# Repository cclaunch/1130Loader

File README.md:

# 1130Loader

This is a minor enhancement to an IBM 1130 that allows users to enter commands from a PC either directly or through a file, entering data words into core. This will be version 5 of the design, a significant change. 

Manually toggling in programs is a time consuming affair, flipping the 16 Console Entry Switches and pushing the Program Start button to enter each word sequentially. Every change in the area of core to be loaded requires that the address be set in those entry switches and the Load IAR button be pressed.

This device utilizes the cycle steal capability of the 1130, where peripheral controllers can read or write locations in memory by causing the CPU to pause while a memory cycle is used for the peripheral, then the CPU instruction processing continues. This is very similar to DMA on a microprocessor. 

When used with a terminal program that will send lines of a text file when it receives the prompt character from the loader, this allows files to be prepared to load into core of the 1130 in a rapid and reliable way. The format of the text file was chosen to match the simh based IBM 1130 Simulator memory dump format, thus programs can be tested on the simulator, dumped to files and loaded onto the physical 1130 system for execution. The format is to place each word as four ASCII characters represening the four hex digits. If the four digit line is prefixed by the command character @, the value is loaded into the 1130 IAR to set the location for subsequent memory words. If the line is prefixed by the command character Z it loads words of 0000 into as many locations as the four hex digits specify. If the command character prefix is =, the four digit value is saved and at the end of the loading, the IAR will be set to this value as the starting point for execution. Finally the command character # entered on a line by itself will toggle the loader to activation or deactivate it. Thus each simulator memory dump file needs to have a # line added at the front and at the end. 

To use the loader, connect a serial connection to the USB connector on the 1130 and open the terminal program. The 1130 must be stopped for this to runction, otherwise nothing special is needed. 

Physically the loader consists of an Arduino Mega 2560 and a custom shield that interfaces it to the IBM 1130. This is mounted on the logic gate B, connected to header boards on the gate which are then connected to individual backplane (board) pins using wirewrap. 

The code allows you to substitute different command characters and change the prompt character.

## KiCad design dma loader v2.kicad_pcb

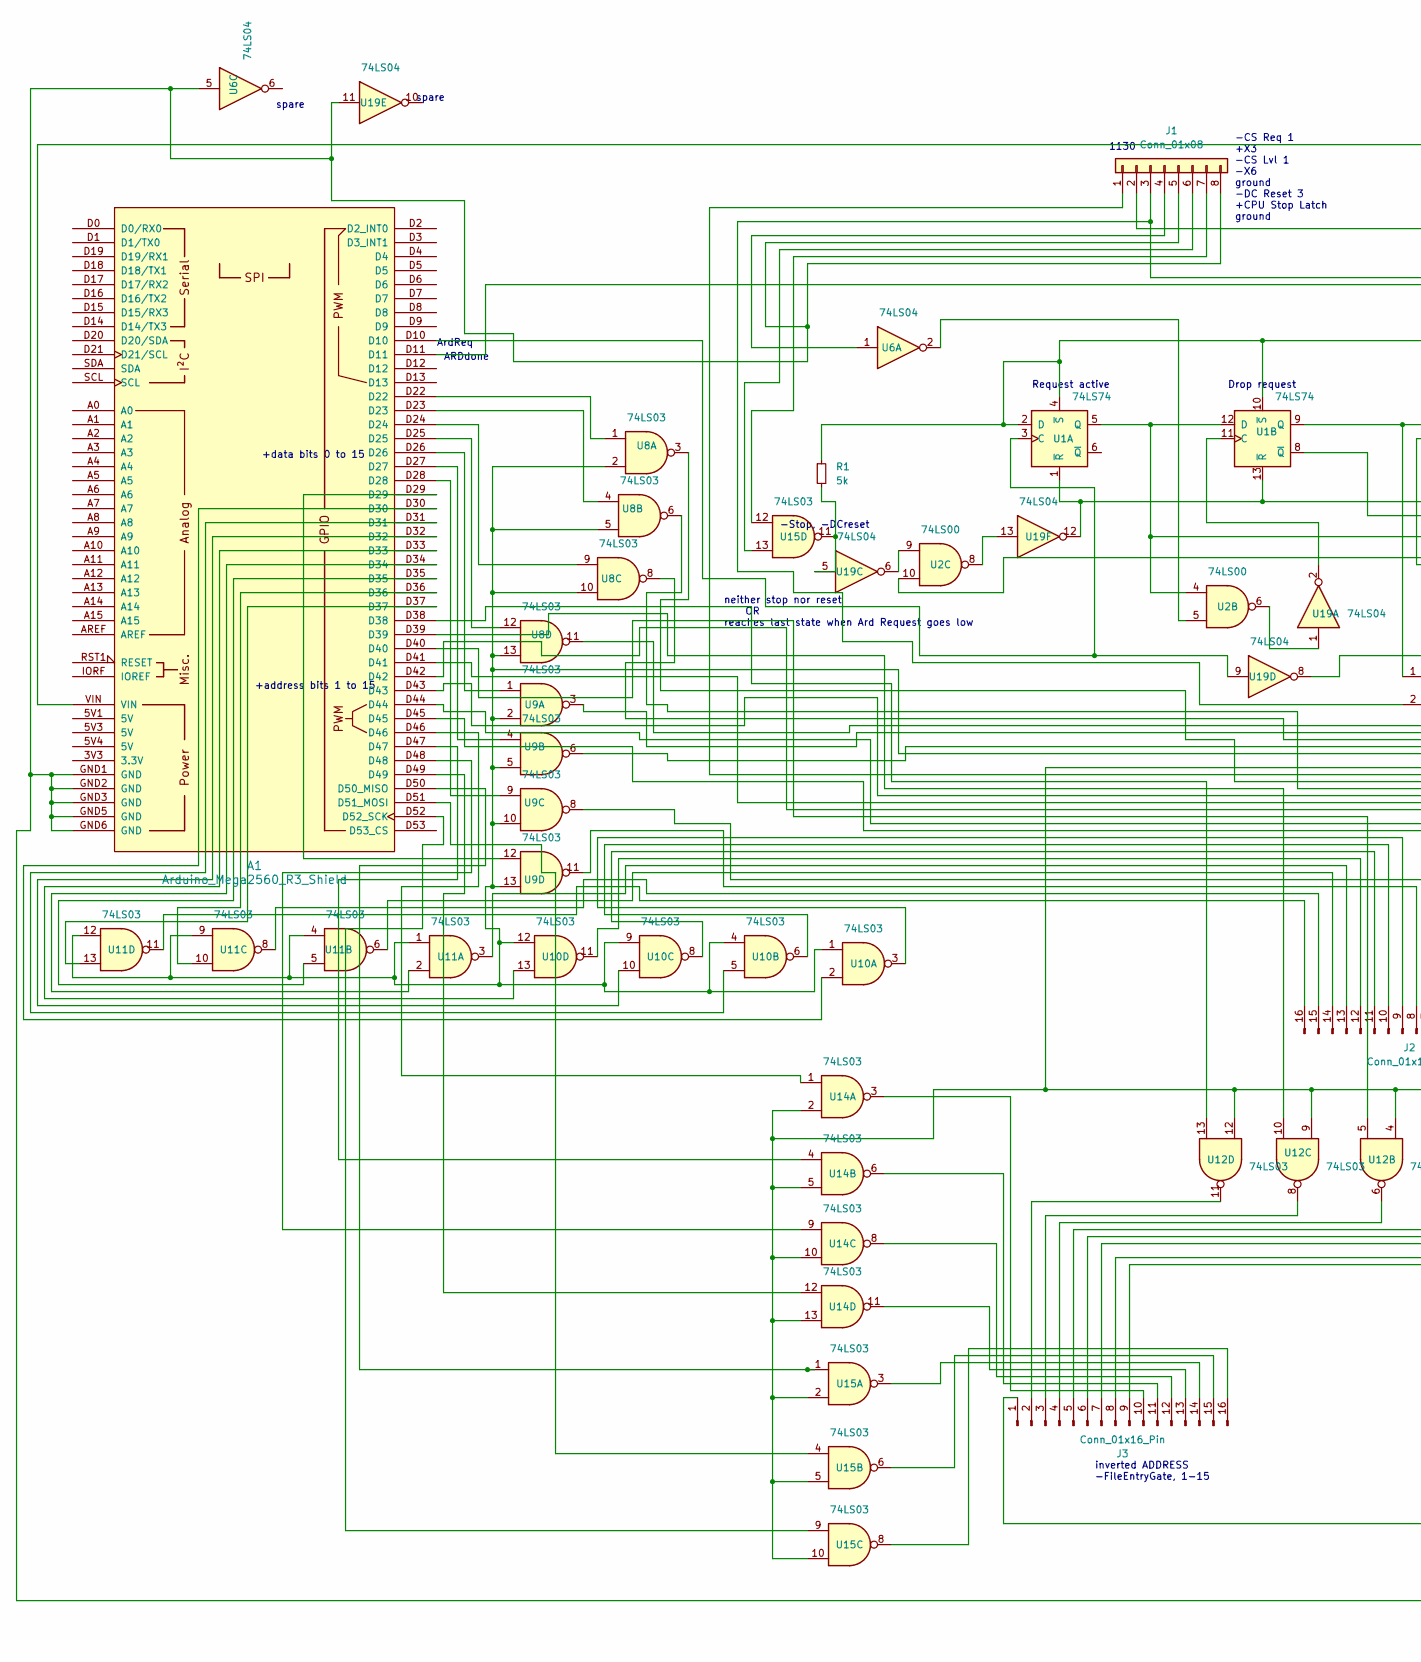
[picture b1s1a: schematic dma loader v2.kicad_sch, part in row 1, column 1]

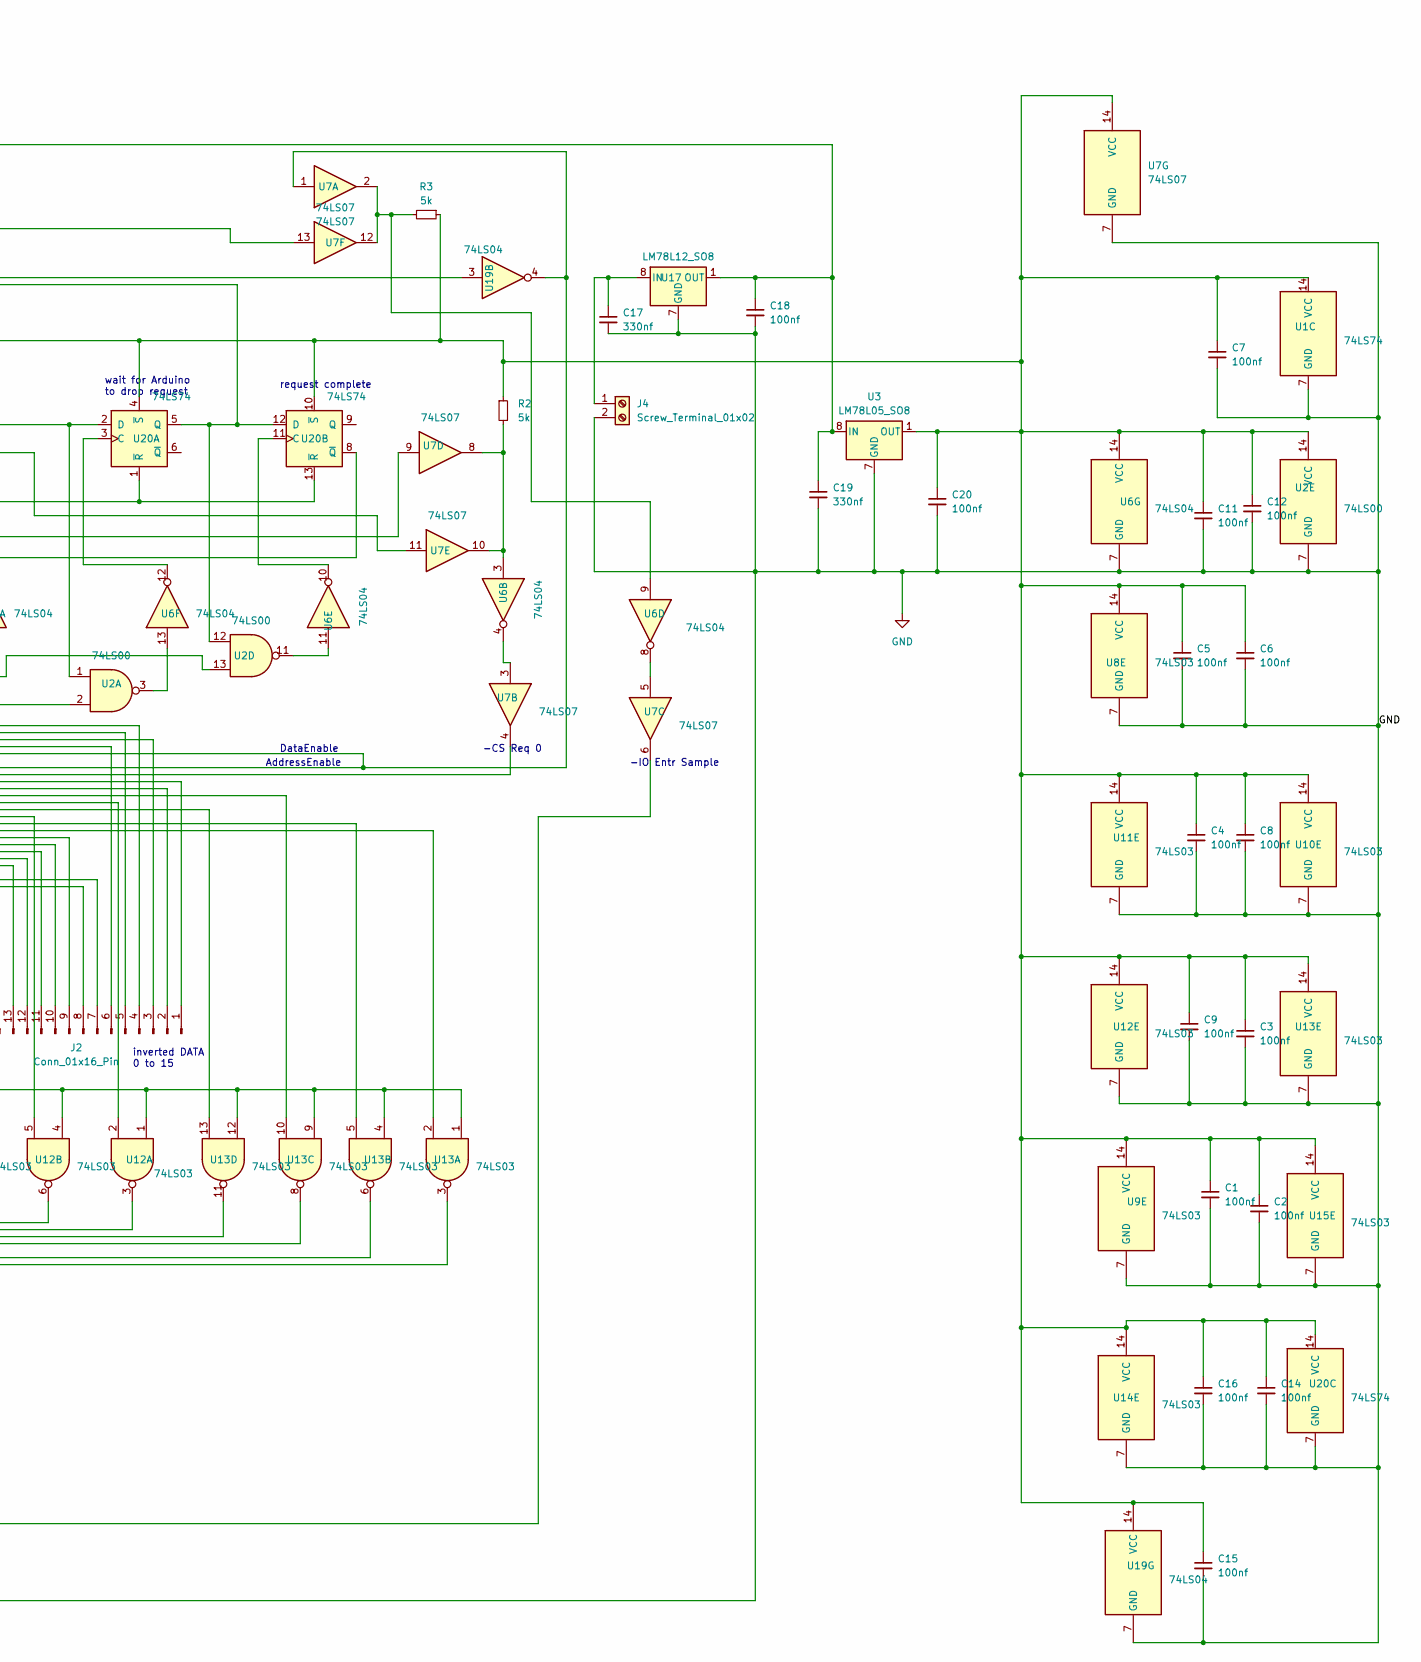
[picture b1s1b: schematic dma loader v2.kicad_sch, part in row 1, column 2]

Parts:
A1: Arduino_Mega2560_R3_Shield
C1, C2, C3, C4, C5, C6, C7, C8, C9, C11, C12, C14, C15, C16, C18, C20: 100nf; C_0805_2012Metric_Pad1.18x1.45mm_HandSolder
C17, C19: 330nf; C_0805_2012Metric_Pad1.18x1.45mm_HandSolder
J1: Conn_01x08; PinHeader_1x08_P2.54mm_Vertical
J2, J3: Conn_01x16_Pin; PinHeader_1x16_P2.54mm_Vertical
J4: Screw_Terminal_01x02; PhoenixContact_MSTBA_2,5_2-G_1x02_P5.00mm_Horizontal
R1, R2, R3: 5k; R_0805_2012Metric_Pad1.20x1.40mm_HandSolder
U1, U20: 74LS74; SOIC-14_3.9x8.7mm_P1.27mm
U2: 74LS00; SOIC-14_3.9x8.7mm_P1.27mm
U3: LM78L05_SO8; SOIC-8_3.9x4.9mm_P1.27mm
U6, U19: 74LS04; SOIC-14_3.9x8.7mm_P1.27mm
U7: 74LS07; SOIC-14_3.9x8.7mm_P1.27mm
U8, U9, U10, U11, U12, U13, U14, U15: 74LS03; SOIC-14_3.9x8.7mm_P1.27mm
U17: LM78L12_SO8; SOIC-8_3.9x4.9mm_P1.27mm

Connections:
GND: A1.GND1 (GND), A1.GND2 (GND), A1.GND3 (GND), A1.GND5 (GND), A1.GND6 (GND), C1.2, C2.2, C3.2, C4.2, C5.2, C6.2, C7.2, C8.2, C9.2, C11.2, C12.2, C14.2, C15.2, C16.2, C17.2, C18.2, C19.2, C20.2, J1.5, J1.8, J4.2, U1.7 (GND), U2.7 (GND), U3.2 (GND), U3.3 (GND), U3.6 (GND), U3.7 (GND), U6.5, U6.7 (GND), U7.7 (GND), U8.7 (GND), U9.7 (GND), U10.7 (GND), U11.7 (GND), U12.7 (GND), U13.7 (GND), U14.7 (GND), U15.7 (GND), U17.2 (GND), U17.3 (GND), U17.6 (GND), U17.7 (GND), U19.7 (GND), U19.11, U20.7 (GND)
unnamed: A1.D50 (D50_MISO), U15.1
unnamed: A1.D51 (D51_MOSI), U15.4
unnamed: A1.D52 (D52_SCK), U15.9
unnamed: A1.D22, U8.1
unnamed: A1.D23, U8.4
unnamed: A1.D24, U8.9
unnamed: A1.D25, U8.12
unnamed: A1.D26, U9.1
unnamed: A1.D27, U9.4
unnamed: A1.D28, U9.9
unnamed: A1.D29, U9.12
unnamed: A1.D30, U10.2
unnamed: A1.D31, U10.5
unnamed: A1.D32, U10.10
unnamed: A1.D33, U10.13
unnamed: A1.D34, U11.2
unnamed: A1.D35, U11.5
unnamed: A1.D36, U11.10
unnamed: A1.D37, U11.13
unnamed: A1.D38, U12.13
unnamed: A1.D39, U12.10
unnamed: A1.D40, U12.5
unnamed: A1.D41, U12.2
unnamed: A1.D42, U13.13
unnamed: A1.D43, U13.10
unnamed: A1.D44, U13.5
unnamed: A1.D45, U13.2
unnamed: A1.D46, U14.1
unnamed: A1.D47, U14.4
unnamed: A1.D48, U14.9
unnamed: A1.D49, U14.12
unnamed: J1.1, U7.4
unnamed: J1.2, U7.13
unnamed: J1.3, U2.2, U19.3
unnamed: J1.4, U6.1
unnamed: J1.6, U15.13
unnamed: J1.7, U15.12
unnamed: J2.1, U8.3
unnamed: J2.2, U8.6
unnamed: J2.3, U8.8
unnamed: J2.4, U8.11
unnamed: J2.5, U9.3
unnamed: J2.6, U9.6
unnamed: J2.7, U9.8
unnamed: J2.8, U9.11
unnamed: J2.9, U10.3
unnamed: J2.10, U10.6
unnamed: J2.11, U10.8
unnamed: J2.12, U10.11
unnamed: J2.13, U11.3
unnamed: J2.14, U11.6
unnamed: J2.15, U11.8
unnamed: J2.16, U11.11
unnamed: J3.1, U7.6
unnamed: J3.2, U12.11
unnamed: J3.3, U12.8
unnamed: J3.4, U12.6
unnamed: J3.5, U12.3
unnamed: J3.6, U13.11
unnamed: J3.7, U13.8
unnamed: J3.8, U13.6
unnamed: J3.9, U13.3
unnamed: J3.10, U14.3
unnamed: J3.11, U14.6
unnamed: J3.12, U14.8
unnamed: J3.13, U14.11
unnamed: J3.14, U15.3
unnamed: J3.15, U15.6
unnamed: J3.16, U15.8
unnamed: C17.1, J4.1, U17.8 (IN)
unnamed: R1.2, U15.11, U19.5
unnamed: R2.2, U6.3, U7.8, U7.10
unnamed: R3.2, U6.9, U7.2, U7.12
unnamed: A1.D10, U1.3 (C), U19.9
unnamed: U1.5 (Q), U1.12 (D), U2.4, U7.9
unnamed: U1.1 (~R), U1.13 (~R), U19.12, U20.1 (~R), U20.13 (~R)
unnamed: U1.11 (C), U19.2
unnamed: U1.9 (Q), U2.1, U20.2 (D)
unnamed: U1.8 (~Q), U7.11
unnamed: U2.3, U6.13
unnamed: U2.5, U6.2
unnamed: U2.11, U6.11
unnamed: U6.4, U7.3
unnamed: U6.8, U7.5
unnamed: U7.1, U8.2, U8.5, U8.10, U8.13, U9.2, U9.5, U9.10, U9.13, U10.1, U10.4, U10.9, U10.12, U11.1, U11.4, U11.9, U11.12, U12.1, U12.4, U12.9, U12.12, U13.1, U13.4, U13.9, U13.12, U14.2, U14.5, U14.10, U14.13, U15.2, U15.5, U15.10, U19.4
unnamed: C1.1, C2.1, C3.1, C4.1, C5.1, C6.1, C7.1, C8.1, C9.1, C11.1, C12.1, C14.1, C15.1, C16.1, C20.1, R1.1, R2.1, R3.1, U1.2 (D), U1.4 (~S), U1.10 (~S), U1.14 (VCC), U2.14 (VCC), U3.1 (OUT), U6.14 (VCC), U7.14 (VCC), U8.14 (VCC), U9.14 (VCC), U10.14 (VCC), U11.14 (VCC), U12.14 (VCC), U13.14 (VCC), U14.14 (VCC), U15.14 (VCC), U19.14 (VCC), U20.4 (~S), U20.10 (~S), U20.14 (VCC)
unnamed: A1.VIN, C18.1, C19.1, U3.8 (IN), U17.1 (OUT)
unnamed: U2.6, U19.1
unnamed: U2.9, U19.6
unnamed: U2.13, U19.8
unnamed: U2.8, U19.13
unnamed: U6.12, U20.3 (C)
unnamed: A1.D11, U2.12, U20.5 (Q), U20.12 (D)
unnamed: U6.10, U20.11 (C)
unnamed: U2.10, U20.8 (~Q)

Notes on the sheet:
+data bits 0 to 15
-CS Req 0
-IO Entr Sample
-Stop, -DCreset
spare
neither stop nor reset OR reaches last state when Ard Request goes low
ARDdone
Request active
1130
AddressEnable
-CS Req 1 +X3 -CS Lvl 1 -X6 ground -DC Reset 3 +CPU Stop Latch ground
+address bits 1 to 15
inverted DATA 0 to 15
request complete
ArdReq
wait for Arduino to drop request
DataEnable
inverted ADDRESS -FileEntryGate, 1-15
Drop request

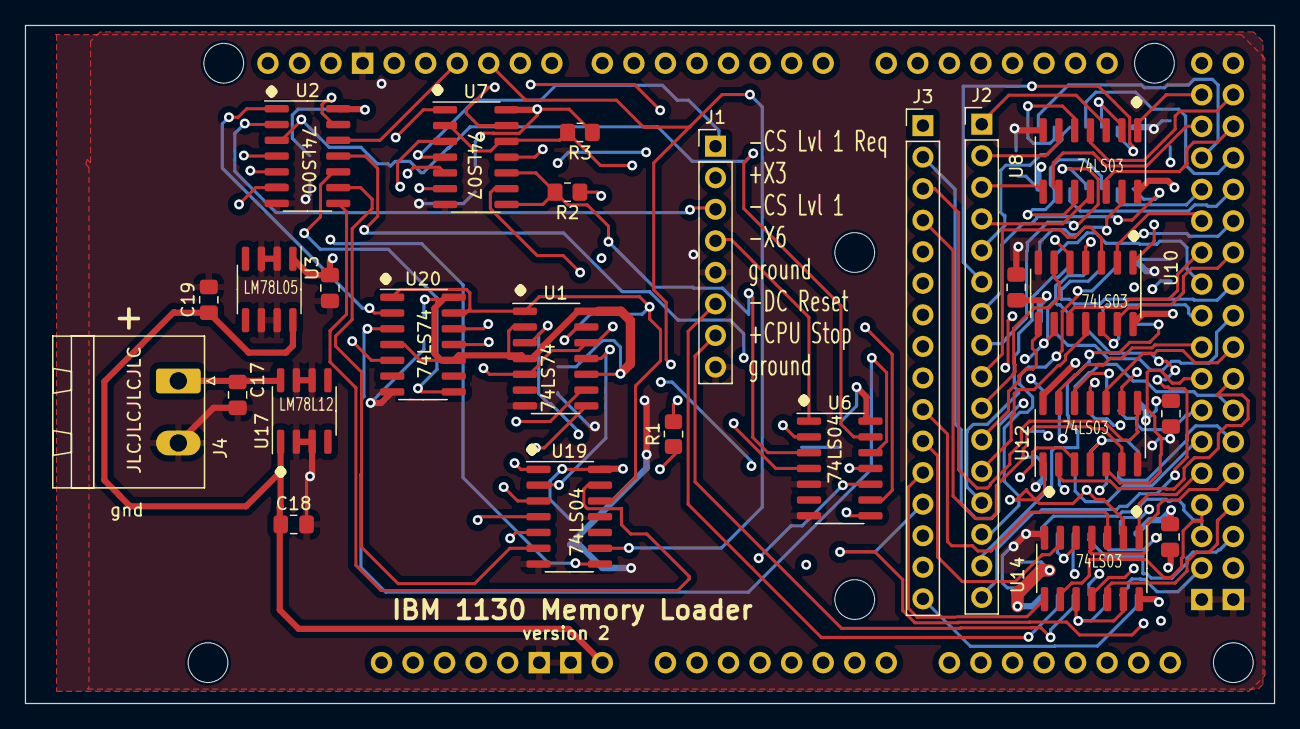
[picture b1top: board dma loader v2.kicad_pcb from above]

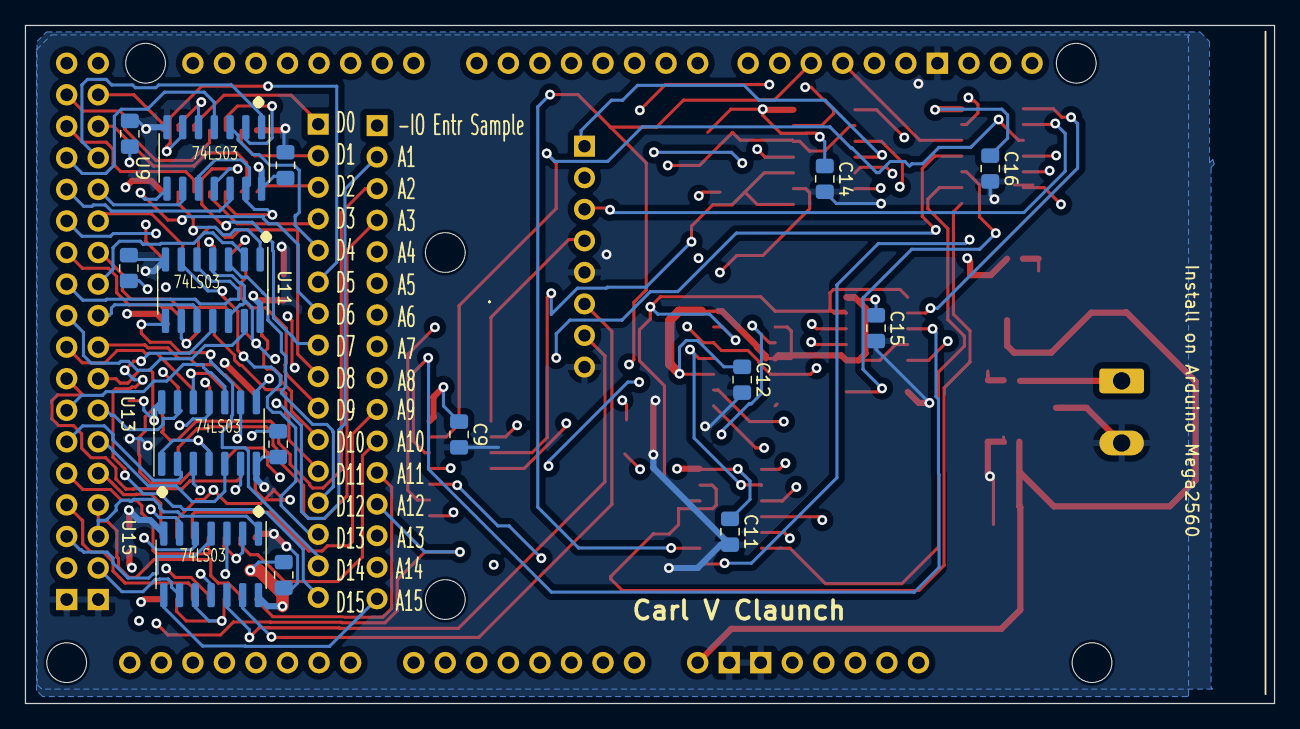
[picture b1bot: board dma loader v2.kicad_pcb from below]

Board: 4 copper layers, 100.6 x 54.6 mm, 42 parts (15 on the bottom side), 96 nets.

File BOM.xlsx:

Part number | Value | Size | Vendor | vendor number
U1 | 74LS74 | 14SOIC | Digikey | 296-14899-1-ND
U2 | 74LS00 | 14SOIC | Digikey | 296-14873-1-ND
U3 | LM78L05 | S08 | Mouser | 926-LM78L05ACMX/NOPB
U6 | 74LS04 | 14SOIC | Digikey | 296-14875-1-ND
U7 | 74LS07 | 14SOIC | Digikey | 296-14877-1-ND
U8 | 74LS03 | 14SOIC | Digikey | 296-33951-5-ND
U9 | 74LS03 | 14SOIC | Digikey | 296-33951-5-ND
U10 | 74LS03 | 14SOIC | Digikey | 296-33951-5-ND
U11 | 74LS03 | 14SOIC | Digikey | 296-33951-5-ND
U12 | 74LS03 | 14SOIC | Digikey | 296-33951-5-ND
U13 | 74LS03 | 14SOIC | Digikey | 296-33951-5-ND
U14 | 74LS03 | 14SOIC | Digikey | 296-33951-5-ND
U15 | 74LS03 | 14SOIC | Digikey | 296-33951-5-ND
U17 | LM78L12 | S08 | Digikey | 296-LM78L12ACMX/NOPBCT-ND
U19 | 74LS04 | 14SOIC | Digikey | 296-14875-1-ND
U20 | 74LS74 | 14SOIC | Digikey | 296-14899-1-ND
R1 | 5K | 0805 | Digikey | 541-CRCW08055K00JNTACT-ND
R2 | 5K | 0805 | Digikey | 541-CRCW08055K00JNTACT-ND
R3 | 5K | 0805 | Digikey | 541-CRCW08055K00JNTACT-ND
J1 | 1x8 | 2.54mm | Digikey | 2057-PH1-08-UA-ND
J2 | 1x16 | 2.54mm | Digikey | 2057-PH1-16-UA-ND
J3 | 1x16 | 2.54mm | Digikey | 2057-PH1-16-UA-ND
J4 | 1x2 |  | Digikey | 277-1236-ND
C1 | 100nf | 0805 | Digikey | 478-KGM21NR71H104KTCT-ND
C2 | 100nf | 0805 | Digikey | 478-KGM21NR71H104KTCT-ND
C3 | 100nf | 0805 | Digikey | 478-KGM21NR71H104KTCT-ND
C4 | 100nf | 0805 | Digikey | 478-KGM21NR71H104KTCT-ND
C5 | 100nf | 0805 | Digikey | 478-KGM21NR71H104KTCT-ND
C6 | 100nf | 0805 | Digikey | 478-KGM21NR71H104KTCT-ND
C7 | 100nf | 0805 | Digikey | 478-KGM21NR71H104KTCT-ND
C8 | 100nf | 0805 | Digikey | 478-KGM21NR71H104KTCT-ND
C9 | 100nf | 0805 | Digikey | 478-KGM21NR71H104KTCT-ND
C11 | 100nf | 0805 | Digikey | 478-KGM21NR71H104KTCT-ND
C12 | 100nf | 0805 | Digikey | 478-KGM21NR71H104KTCT-ND
C13 | 100nf | 0805 | Digikey | 478-KGM21NR71H104KTCT-ND
C14 | 100nf | 0805 | Digikey | 478-KGM21NR71H104KTCT-ND
C15 | 100nf | 0805 | Digikey | 478-KGM21NR71H104KTCT-ND
C16 | 100nf | 0805 | Digikey | 478-KGM21NR71H104KTCT-ND
C17 | 330nf | 0805 | Digikey | 490-14413-1-ND
C18 | 100nf | 0805 | Digikey | 478-KGM21NR71H104KTCT-ND
C19 | 330nf | 0805 | Digikey | 490-14413-1-ND
C20 | 100nf | 0805 | Digikey | 478-KGM21NR71H104KTCT-ND
A1 | 1x10 | 2.54mm | Digikey | 2057-PH1-10-UA-ND
A2 | 1x8 | 2.54mm | Digikey | 2057-PH1-08-UA-ND
A3 | 1x8 | 2.54mm | Digikey | 2057-PH1-08-UA-ND
A4 | 2x20 | 2.54mm | Digikey | 2057-PH2-20-UA-ND
A5 | 1x8 | 2.54mm | Digikey | 2057-PH1-08-UA-ND
A6 | 1x8 | 2.54mm | Digikey | 2057-PH1-08-UA-ND
A7 | 1x8 | 2.54mm | Digikey | 2057-PH1-08-UA-ND
P1 | 1x8 | 2.54mm | Mouser | 200-IDSS08D2000GR
P2 | 1x16 | 2.54mm | Mouser | 200-IDSS16D2000
P3 | 1x16 | 2.54mm | Mouser | 200-IDSS16D2000

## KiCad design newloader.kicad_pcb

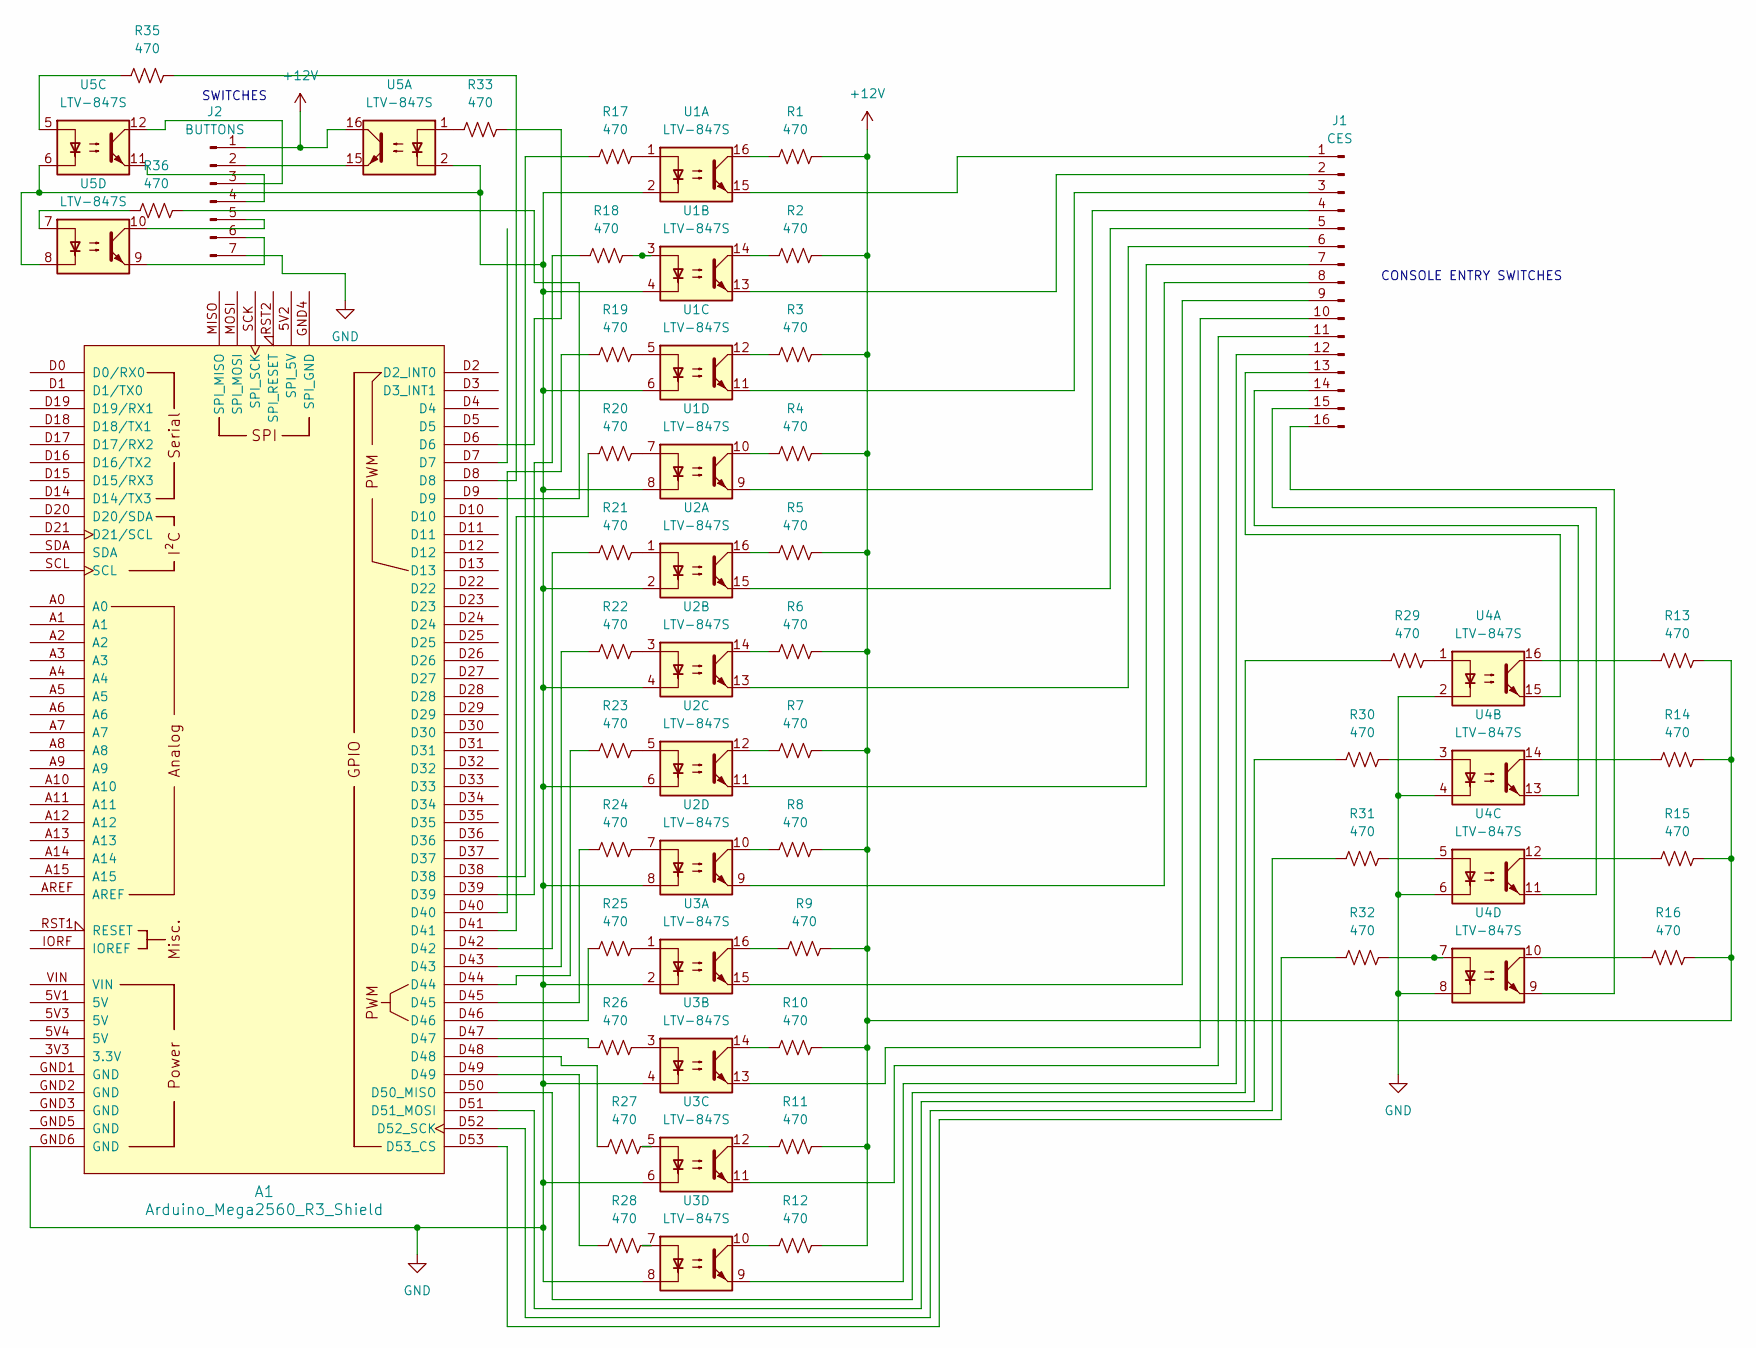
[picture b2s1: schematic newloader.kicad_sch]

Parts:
A1: Arduino_Mega2560_R3_Shield
J1: CES; PinHeader_1x16_P2.54mm_Vertical_SMD_Pin1Right
J2: BUTTONS; PinHeader_1x07_P2.54mm_Vertical_SMD_Pin1Left
R1, R2, R3, R4, R5, R6, R7, R8, R9, R10, R11, R12, R13, R14, R15, R16, R17, R18, R19, R20, R21, R22, R23, R24, R25, R26, R27, R28, R29, R30, R31, R32, R33, R35, R36: 470; R_0805_2012Metric
U1, U2, U3, U4, U5: LTV-847S; SMDIP-16_W9.53mm

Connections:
+12V: J2.1, R1.1, R2.1, R3.1, R4.1, R5.1, R6.1, R7.1, R8.1, R9.1, R10.1, R11.1, R12.1, R13.1, R14.1, R15.1, R16.1, U5.16
GND: A1.GND6 (GND), J2.7, U1.2, U1.4, U1.6, U1.8, U2.2, U2.4, U2.6, U2.8, U3.2, U3.4, U3.6, U3.8, U4.2, U4.4, U4.6, U4.8, U5.2, U5.6, U5.8
unnamed: A1.D50 (D50_MISO), R29.2
unnamed: A1.D51 (D51_MOSI), R30.2
unnamed: A1.D52 (D52_SCK), R31.2
unnamed: A1.D53 (D53_CS), R32.2
unnamed: A1.D6, R33.1
unnamed: A1.D8, R35.1
unnamed: A1.D9, R36.1
unnamed: A1.D38, R17.2
unnamed: A1.D39, R18.2
unnamed: A1.D40, R19.2
unnamed: A1.D41, R20.2
unnamed: A1.D42, R21.2
unnamed: A1.D43, R22.2
unnamed: A1.D44, R23.2
unnamed: A1.D45, R24.2
unnamed: A1.D46, R25.2
unnamed: A1.D47, R26.2
unnamed: A1.D48, R27.2
unnamed: A1.D49, R28.2
unnamed: J1.1, U1.15
unnamed: J1.2, U1.13
unnamed: J1.3, U1.11
unnamed: J1.4, U1.9
unnamed: J1.5, U2.15
unnamed: J1.6, U2.13
unnamed: J1.7, U2.11
unnamed: J1.8, U2.9
unnamed: J1.9, U3.15
unnamed: J1.10, U3.13
unnamed: J1.11, U3.11
unnamed: J1.12, U3.9
unnamed: J1.13, U4.15
unnamed: J1.14, U4.13
unnamed: J1.15, U4.11
unnamed: J1.16, U4.9
unnamed: J2.2, U5.15
unnamed: J2.3, U5.12
unnamed: J2.4, U5.11
unnamed: J2.5, U5.10
unnamed: J2.6, U5.9
unnamed: R1.2, U1.16
unnamed: R2.2, U1.14
unnamed: R3.2, U1.12
unnamed: R4.2, U1.10
unnamed: R5.2, U2.16
unnamed: R6.2, U2.14
unnamed: R7.2, U2.12
unnamed: R8.2, U2.10
unnamed: R9.2, U3.16
unnamed: R10.2, U3.14
unnamed: R11.2, U3.12
unnamed: R12.2, U3.10
unnamed: R13.2, U4.16
unnamed: R14.2, U4.14
unnamed: R15.2, U4.12
unnamed: R16.2, U4.10
unnamed: R17.1, U1.1
unnamed: R18.1, U1.3
unnamed: R19.1, U1.5
unnamed: R20.1, U1.7
unnamed: R21.1, U2.1
unnamed: R22.1, U2.3
unnamed: R23.1, U2.5
unnamed: R24.1, U2.7
unnamed: R25.1, U3.1
unnamed: R26.1, U3.3
unnamed: R27.1, U3.5
unnamed: R28.1, U3.7
unnamed: R29.1, U4.1
unnamed: R30.1, U4.3
unnamed: R31.1, U4.5
unnamed: R32.1, U4.7
unnamed: R33.2, U5.1
unnamed: R35.2, U5.5
unnamed: R36.2, U5.7

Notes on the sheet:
SWITCHES
CONSOLE ENTRY SWITCHES

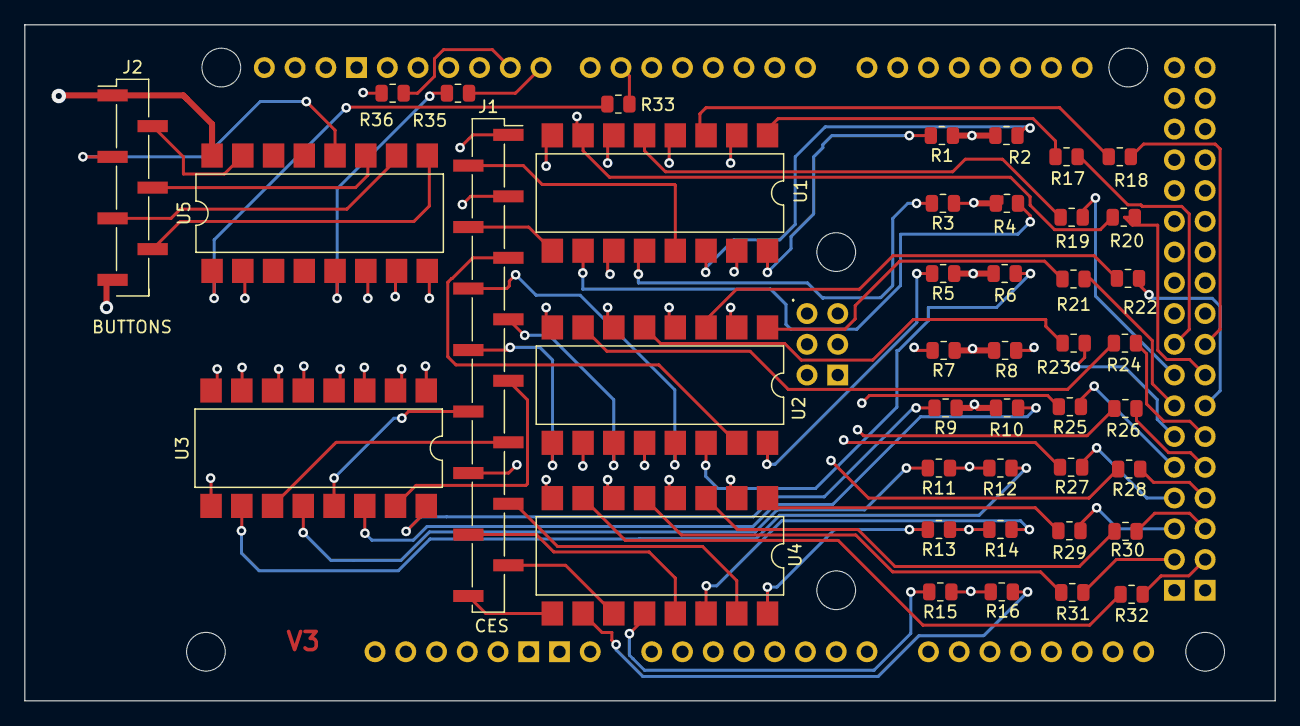
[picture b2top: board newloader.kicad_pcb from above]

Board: 4 copper layers, 103.3 x 55.8 mm, 43 parts (0 on the bottom side), 77 nets.

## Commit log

2018-05-01 Add files via upload
    Fixed defect in the order of deactivation compared to loading the IAR
2023-11-15 Document Version 2 of the project, partial update
2023-11-15 tweak to document
2023-11-15 Version 2 of Arduino code
2023-11-15 Version 2 update
2023-11-15 First upload of V2 shield PCB layout (KiCAD)
2023-11-15 Schematic of V2 shield (KiCAD)
2023-11-15 Gerber files for V2 shield PCB
2023-11-16 Clear saved address on new activation
    The saved address from a prior session will be used to load the IAR on a new session when we deactivate. The solution is to clear out the saved address on each activation.
2023-11-16 Fixed issue when USB and +12V both power the Arduino
2023-11-16 Changed PCB to fix multiple powering issue
2023-11-19 updating PCB
2023-11-19 updating schematic
2023-11-19 updating PCB gerbers
2023-11-19 Updated corrected V2 design
2023-11-19 Gerbers and drills related to corrected V2 design
2023-12-05 minor tweak to document
2023-12-05 V3 for easier parts purchase of 16 pin header
2023-12-05 V3 for easier parts purchase for 16 pin header
2023-12-05 removed V2 of pcb
2024-03-05 updated to avoid wiring error in 1130
2024-03-05 Improvements to behavior with different terminals
2024-03-12 V4 with alternate wiring to 1130
    Prior wiring method allowed bounce to show up as multiple button presses. New method solves that issue.
2024-03-12 V4 describing new wiring to 1130
2024-03-12 Update using 1130loader.txt V4
    Minor edits and update version number to 4
2024-03-12 Newest PCB gerber and drill files for V4
2024-03-12 V4 of code to match other files
    New PCB alters design, new wiring method from the loader to the IBM 1130 and improved code
2024-03-12 Update README.md for V4
2024-03-12 Explanation for mounting the loader
2024-03-12 project now complete with upload of mounting document
2024-03-13 Minor enhancement
    Ignores leading spaces on command lines, as some simulator memory dumps put a space before lines loading data values
2024-03-15 Remove superfluous message to terminal
    when the loader skips leading spaces on command lines, it issued a comment that this had taken place. This is unnecessary and clogs the terminal session. removed the println
2024-03-15 Added information on powering the Arduino
    Made the power connections to the Arduino clearer
2024-05-26 Alert builders of new version coming using DMA
2024-09-26 Update README.md
    DMA/Cycle Steal loader tested and working well
2024-10-19 Corrected errors within installation instructions
